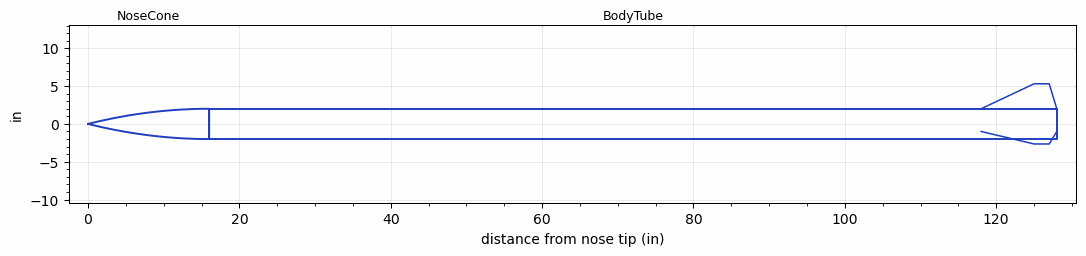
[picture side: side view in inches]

<RASAeroDocument>
 <FileVersion>2</FileVersion>
 <RocketDesign>
  <NoseCone>
   <Length>16</Length>
   <Diameter>4</Diameter>
   <Shape>Parabolic</Shape>
   <Location>0</Location>
  </NoseCone>
  <BodyTube>
   <Length>112</Length>
   <Diameter>4</Diameter>
   <Location>16</Location>
   <Fin>
    <Count>3</Count>
    <Chord>10</Chord>
    <Span>3.3</Span>
    <SweepDistance>7</SweepDistance>
    <TipChord>2</TipChord>
    <Thickness>0.25</Thickness>
    <LERadius>0.125</LERadius>
    <Location>10</Location>
    <AirfoilSection>Double Wedge</AirfoilSection>
    <FX1>1</FX1>
   </Fin>
  </BodyTube>
  <Surface>Camouflage Paint</Surface>
  <ModifiedBarrowman>False</ModifiedBarrowman>
  <Turbulence>False</Turbulence>
  <UseBooster1>False</UseBooster1>
  <UseBooster2>False</UseBooster2>
 </RocketDesign>
 <LaunchSite>
  <Altitude>5000</Altitude>
  <Pressure>0</Pressure>
  <RodAngle>7</RodAngle>
  <RodLength>18</RodLength>
  <Temperature>95</Temperature>
  <WindSpeed>8</WindSpeed>
 </LaunchSite>
 <Recovery>
  <Altitude1>1000</Altitude1>
  <Altitude2>1000</Altitude2>
  <DeviceType1>None</DeviceType1>
  <DeviceType2>None</DeviceType2>
  <Event1>False</Event1>
  <Event2>False</Event2>
  <Size1>1</Size1>
  <Size2>1</Size2>
  <EventType1>None</EventType1>
  <EventType2>None</EventType2>
  <CD1>1.33</CD1>
  <CD2>1.33</CD2>
 </Recovery>
 <SimulationList>
  <Simulation>
   <SustainerEngine>N2900-CL  (CTI)</SustainerEngine>
   <SustainerLaunchWt>59.3</SustainerLaunchWt>
   <SustainerNozzleDiameter>2</SustainerNozzleDiameter>
   <SustainerCG>76.1</SustainerCG>
   <SustainerIgnitionDelay>0</SustainerIgnitionDelay>
   <Booster1SeparationDelay>0</Booster1SeparationDelay>
   <Booster1IgnitionDelay>0</Booster1IgnitionDelay>
   <IncludeBooster1>False</IncludeBooster1>
   <Booster2Delay>0</Booster2Delay>
   <IncludeBooster2>False</IncludeBooster2>
   <TimetoApogee>50.43754</TimetoApogee>
   <MaxAltitude>44410.77</MaxAltitude>
   <MaxVelocity>2187.81</MaxVelocity>
  </Simulation>
  <Simulation>
   <SustainerEngine>N2900-CL  (CTI)</SustainerEngine>
   <SustainerLaunchWt>60.3</SustainerLaunchWt>
   <SustainerNozzleDiameter>2</SustainerNozzleDiameter>
   <SustainerCG>76.1</SustainerCG>
   <SustainerIgnitionDelay>0</SustainerIgnitionDelay>
   <Booster1SeparationDelay>0</Booster1SeparationDelay>
   <Booster1IgnitionDelay>0</Booster1IgnitionDelay>
   <IncludeBooster1>False</IncludeBooster1>
   <Booster2Delay>0</Booster2Delay>
   <IncludeBooster2>False</IncludeBooster2>
   <TimetoApogee>50.05761</TimetoApogee>
   <MaxAltitude>43537.22</MaxAltitude>
   <MaxVelocity>2147.031</MaxVelocity>
  </Simulation>
  <Simulation>
   <SustainerEngine>N2900-CL  (CTI)</SustainerEngine>
   <SustainerLaunchWt>61.3</SustainerLaunchWt>
   <SustainerNozzleDiameter>2</SustainerNozzleDiameter>
   <SustainerCG>76.1</SustainerCG>
   <SustainerIgnitionDelay>0</SustainerIgnitionDelay>
   <Booster1SeparationDelay>0</Booster1SeparationDelay>
   <Booster1IgnitionDelay>0</Booster1IgnitionDelay>
   <IncludeBooster1>False</IncludeBooster1>
   <Booster2Delay>0</Booster2Delay>
   <IncludeBooster2>False</IncludeBooster2>
   <TimetoApogee>49.68767</TimetoApogee>
   <MaxAltitude>42686.42</MaxAltitude>
   <MaxVelocity>2107.649</MaxVelocity>
  </Simulation>
  <Simulation>
   <SustainerEngine>N2900-CL  (CTI)</SustainerEngine>
   <SustainerLaunchWt>62.3</SustainerLaunchWt>
   <SustainerNozzleDiameter>2</SustainerNozzleDiameter>
   <SustainerCG>76.1</SustainerCG>
   <SustainerIgnitionDelay>0</SustainerIgnitionDelay>
   <Booster1SeparationDelay>0</Booster1SeparationDelay>
   <Booster1IgnitionDelay>0</Booster1IgnitionDelay>
   <IncludeBooster1>False</IncludeBooster1>
   <Booster2Delay>0</Booster2Delay>
   <IncludeBooster2>False</IncludeBooster2>
   <TimetoApogee>49.32773</TimetoApogee>
   <MaxAltitude>41859.71</MaxAltitude>
   <MaxVelocity>2069.561</MaxVelocity>
  </Simulation>
  <Simulation>
   <SustainerEngine>N2900-CL  (CTI)</SustainerEngine>
   <SustainerLaunchWt>64.3</SustainerLaunchWt>
   <SustainerNozzleDiameter>2</SustainerNozzleDiameter>
   <SustainerCG>76.1</SustainerCG>
   <SustainerIgnitionDelay>0</SustainerIgnitionDelay>
   <Booster1SeparationDelay>0</Booster1SeparationDelay>
   <Booster1IgnitionDelay>0</Booster1IgnitionDelay>
   <IncludeBooster1>False</IncludeBooster1>
   <Booster2Delay>0</Booster2Delay>
   <IncludeBooster2>False</IncludeBooster2>
   <TimetoApogee>48.60785</TimetoApogee>
   <MaxAltitude>40261.44</MaxAltitude>
   <MaxVelocity>1997.089</MaxVelocity>
  </Simulation>
  <Simulation>
   <SustainerEngine>N2900-CL  (CTI)</SustainerEngine>
   <SustainerLaunchWt>69.3</SustainerLaunchWt>
   <SustainerNozzleDiameter>2</SustainerNozzleDiameter>
   <SustainerCG>76.1</SustainerCG>
   <SustainerIgnitionDelay>0</SustainerIgnitionDelay>
   <Booster1SeparationDelay>0</Booster1SeparationDelay>
   <Booster1IgnitionDelay>0</Booster1IgnitionDelay>
   <IncludeBooster1>False</IncludeBooster1>
   <Booster2Delay>0</Booster2Delay>
   <IncludeBooster2>False</IncludeBooster2>
   <TimetoApogee>46.88814</TimetoApogee>
   <MaxAltitude>36607.18</MaxAltitude>
   <MaxVelocity>1834.793</MaxVelocity>
  </Simulation>
 </SimulationList>
</RASAeroDocument>
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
